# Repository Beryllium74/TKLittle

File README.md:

# TKLittle
My first custom keyboard layout, fully designed and created by me just as a fun learning experience.

The name TKLittle comes from the layout, inspiered by my 2 favorite layouts: Tkl and 40%(with a little opional HHKB-like bottom row thrown into in).

The pcb is made in Kicad 6 using Klepcbgen by Jeroen Bouwens as a starting point, but with a pro micro insted of an integrated chip.

The case is a top mounted stacked acrylic case made with the help of http://builder.swillkb.com/

Bottom layer, will be 3mm think in clear acrylic to show the bottom silkscreen of the pcb

Middle layer, 5mm thick frosted acrylic, with cutout wide enough to fit the pro micro so its closer to the edge so that it can use different cables easily

Plate, 3mm thick frosted acrylic, with 7u spacebar cutuouts and opion for non-HHKB layout

Top plate,5mm thick frosted acrylic with HHKB blockers.

The case should be mounted with 6 M2x18 bolts with nuts at the end, and for feen im gonna put some silicon feet instead of acyllic.

As i've said this is just a fun project, but i would like to learn from is it so i would if anyone with a bit more experience could give me some feedback on it before i spend the money to turn it into a reality
I have experience hand wiring multiple boards and ive made my own 3d printed cases before, so i kinda know what im doing, but its my first time working with Kicad so this is what im most worried about.

(obligatory language disclamer: english is not my first language so sorry if there are any spelling or grammar mistakes(but i do accept critisims as i need to get better)

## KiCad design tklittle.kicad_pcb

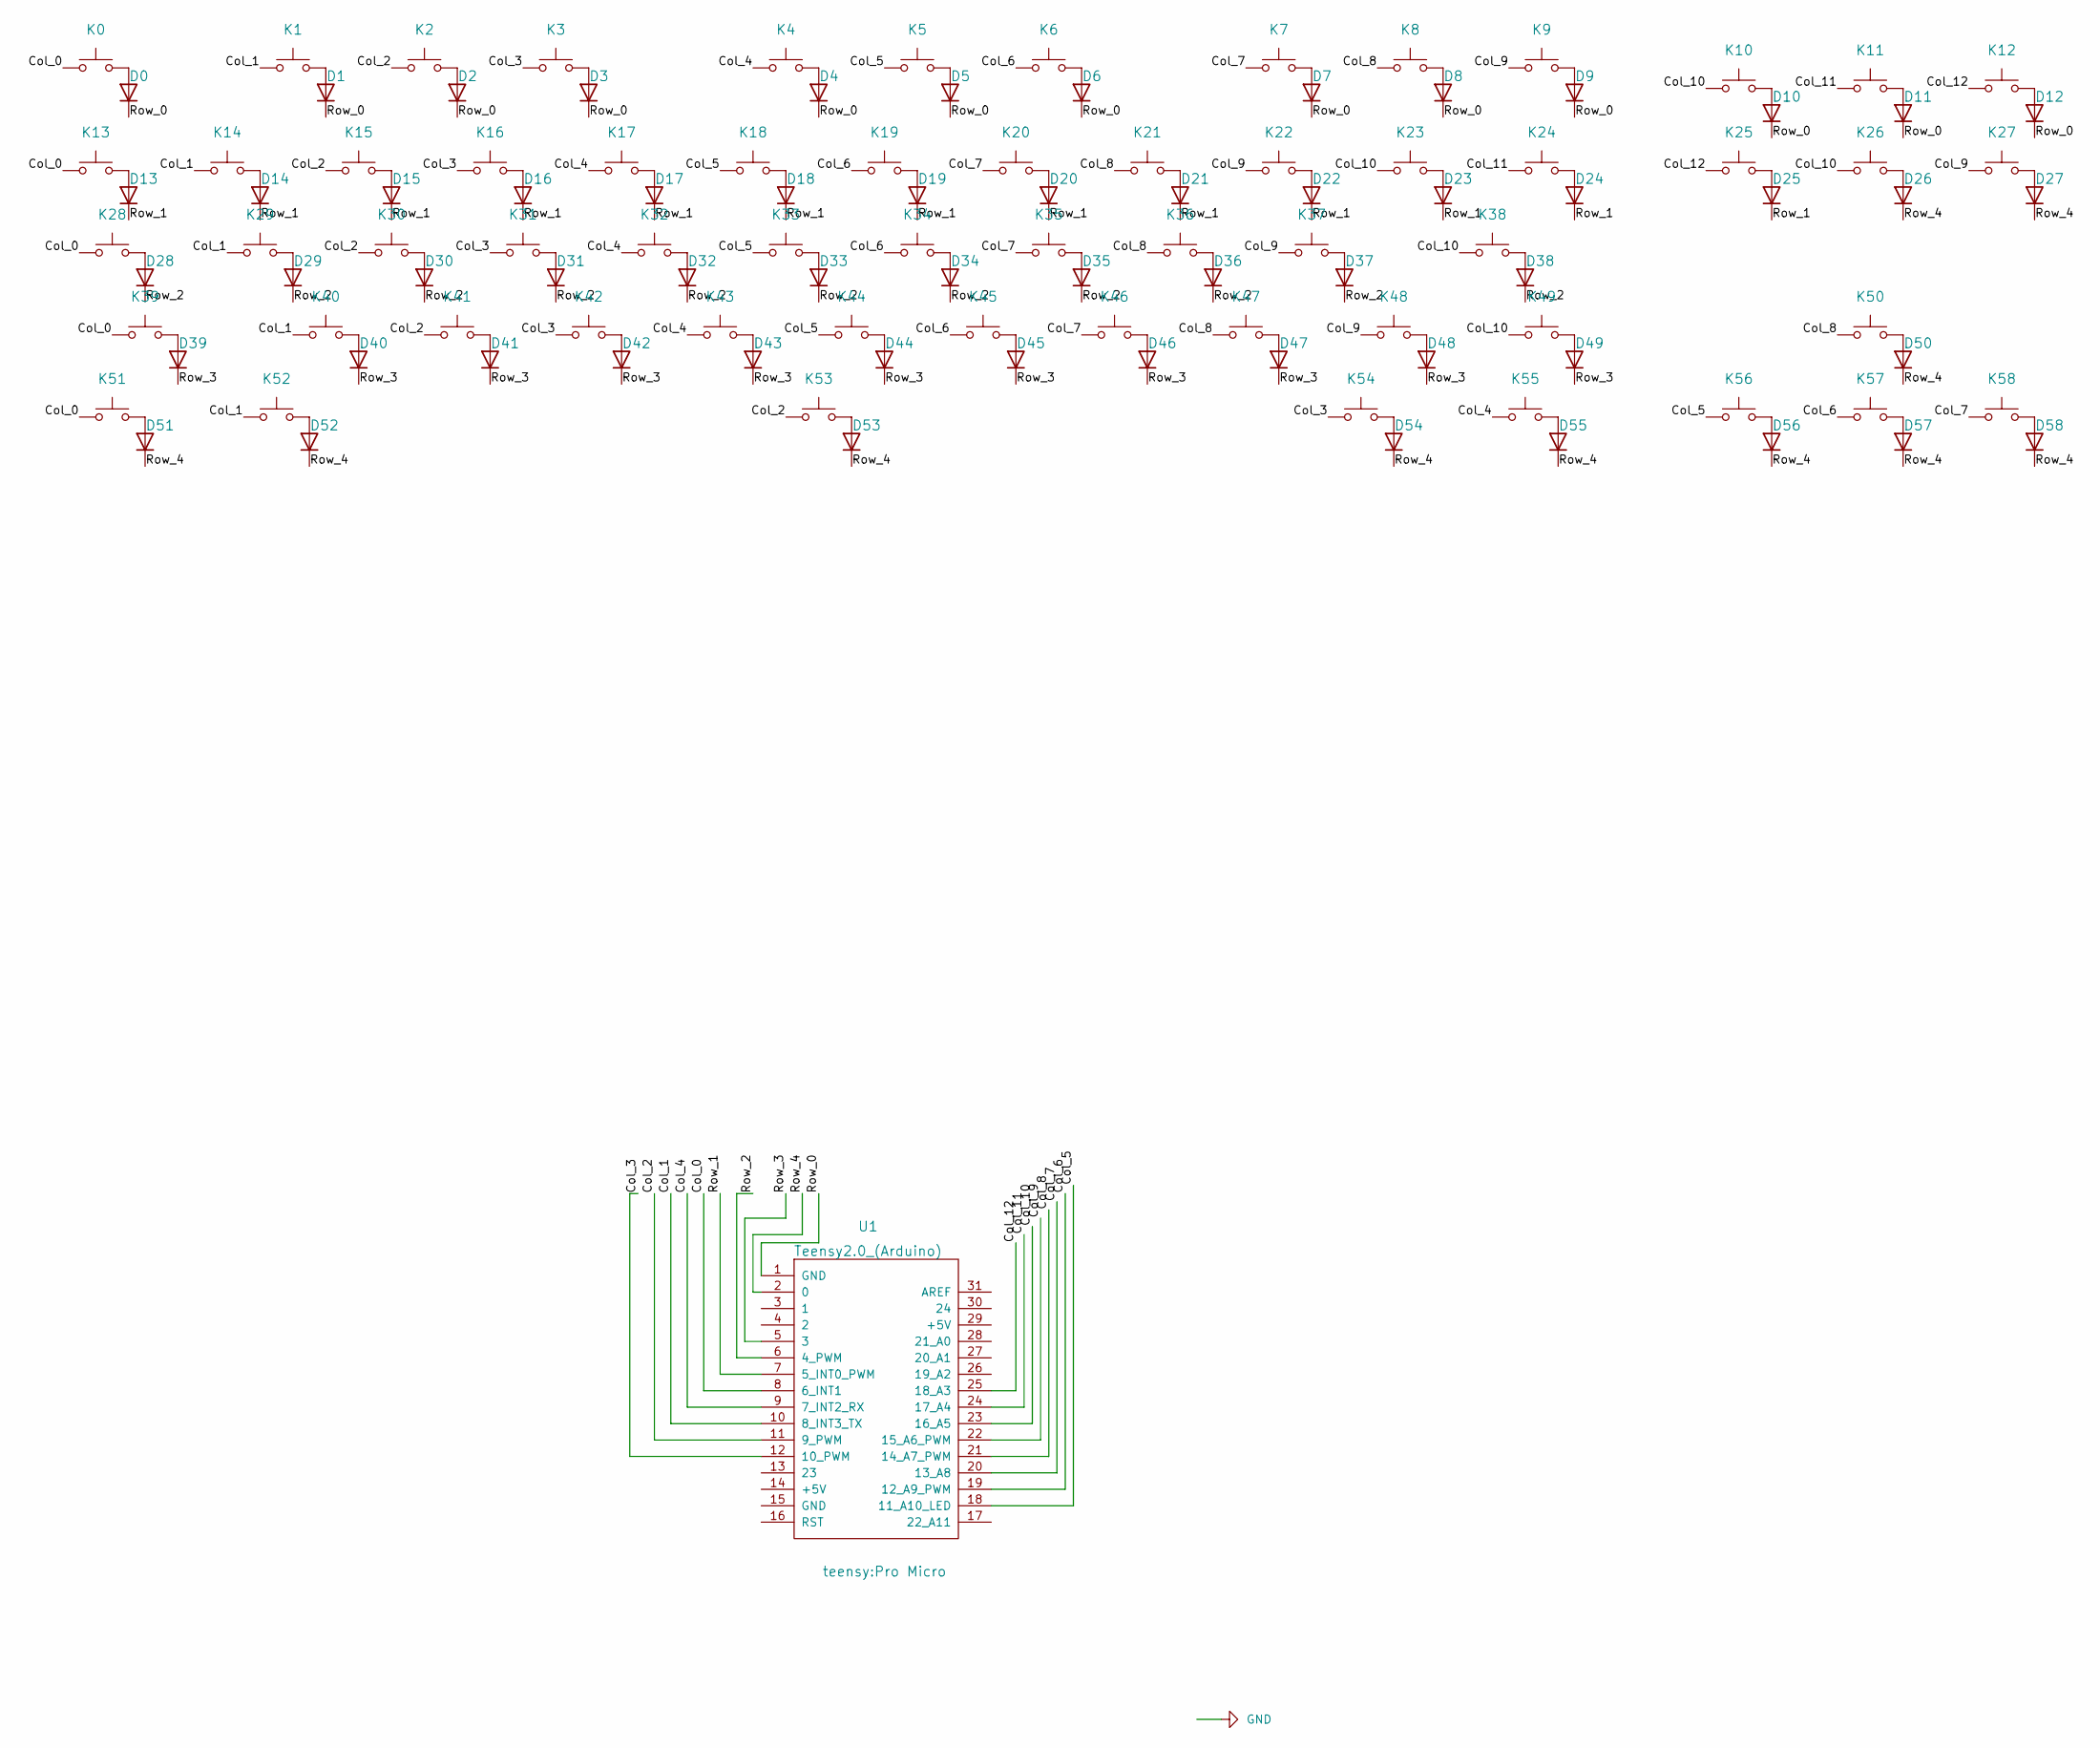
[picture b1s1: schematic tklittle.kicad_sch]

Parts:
D0, D1, D2, D3, D4, D5, D6, D7, D8, D9, D10, D11, D12, D13, D14, D15, D16, D17, D18, D19, D20, D21, D22, D23, D24, D25, D26, D27, D28, D29, D30, D31, D32, D33, D34, D35, D36, D37, D38, D39, D40, D41, D42, D43, D44, D45, D46, D47, D48, D49, D50, D51, D52, D53, D54, D55, D56, D57, D58: D; D_0805_2012Metric_Pad1.15x1.40mm_HandSolder
K0: 1; SW_Cherry_MX_1.00u_PCB
K1: 2; SW_Cherry_MX_1.00u_PCB
K2: 3; SW_Cherry_MX_1.00u_PCB
K3: 4; SW_Cherry_MX_1.00u_PCB
K4: 5; SW_Cherry_MX_1.00u_PCB
K5: 6; SW_Cherry_MX_1.00u_PCB
K6: 7; SW_Cherry_MX_1.00u_PCB
K7: 8; SW_Cherry_MX_1.00u_PCB
K8: 9; SW_Cherry_MX_1.00u_PCB
K9: 0; SW_Cherry_MX_1.00u_PCB
K10: insert; SW_Cherry_MX_1.00u_PCB
K11: Home; SW_Cherry_MX_1.00u_PCB
K12: Pgup; SW_Cherry_MX_1.00u_PCB
K13: Esc; SW_Cherry_MX_1.00u_PCB
K14: Q; SW_Cherry_MX_1.00u_PCB
K15: W; SW_Cherry_MX_1.00u_PCB
K16: E; SW_Cherry_MX_1.00u_PCB
K17: R; SW_Cherry_MX_1.00u_PCB
K18: T; SW_Cherry_MX_1.00u_PCB
K19: Y; SW_Cherry_MX_1.00u_PCB
K20: U; SW_Cherry_MX_1.00u_PCB
K21: I; SW_Cherry_MX_1.00u_PCB
K22: O; SW_Cherry_MX_1.00u_PCB
K23: P; SW_Cherry_MX_1.00u_PCB
K24: Back<br>Space; SW_Cherry_MX_1.00u_PCB
K25: Delete; SW_Cherry_MX_1.00u_PCB
K26: Emd; SW_Cherry_MX_1.00u_PCB
K27: PgDn; SW_Cherry_MX_1.00u_PCB
K28: Tab; SW_Cherry_MX_1.25u_PCB
K29: A; SW_Cherry_MX_1.00u_PCB
K30: S; SW_Cherry_MX_1.00u_PCB
K31: D; SW_Cherry_MX_1.00u_PCB
K32: F; SW_Cherry_MX_1.00u_PCB
K33: G; SW_Cherry_MX_1.00u_PCB
K34: H; SW_Cherry_MX_1.00u_PCB
K35: J; SW_Cherry_MX_1.00u_PCB
K36: K; SW_Cherry_MX_1.00u_PCB
K37: L; SW_Cherry_MX_1.00u_PCB
K38: Enter; SW_Cherry_MX_1.75u_PCB
K39: Shift; SW_Cherry_MX_1.75u_PCB
K40: Z; SW_Cherry_MX_1.00u_PCB
K41: X; SW_Cherry_MX_1.00u_PCB
K42: C; SW_Cherry_MX_1.00u_PCB
K43: V; SW_Cherry_MX_1.00u_PCB
K44: B; SW_Cherry_MX_1.00u_PCB
K45: N; SW_Cherry_MX_1.00u_PCB
K46: M; SW_Cherry_MX_1.00u_PCB
K47: <,.; SW_Cherry_MX_1.00u_PCB
K48: Shift; SW_Cherry_MX_1.25u_PCB
K49: Fn; SW_Cherry_MX_1.00u_PCB
K50: up; SW_Cherry_MX_1.00u_PCB
K51, K55: Super; SW_Cherry_MX_1.25u_PCB
K52, K54: Meta; SW_Cherry_MX_1.25u_PCB
K53: Blank; SW_Cherry_MX_6.25u_PCB
K56: left; SW_Cherry_MX_1.00u_PCB
K57: down; SW_Cherry_MX_1.00u_PCB
K58: right; SW_Cherry_MX_1.00u_PCB
U1: Teensy2.0_(Arduino); Pro Micro

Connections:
/Col_0: K0.1, K13.1, K28.1, K39.1, K51.1, U1.8 (6_INT1)
/Col_1: K1.1, K14.1, K29.1, K40.1, K52.1, U1.10 (8_INT3_TX)
/Col_2: K2.1, K15.1, K30.1, K41.1, K53.1, U1.11 (9_PWM)
/Col_3: K3.1, K16.1, K31.1, K42.1, K54.1, U1.12 (10_PWM)
/Col_4: K4.1, K17.1, K32.1, K43.1, K55.1, U1.9 (7_INT2_RX)
/Col_5: K5.1, K18.1, K33.1, K44.1, K56.1, U1.18 (11_A10_LED)
/Col_6: K6.1, K19.1, K34.1, K45.1, K57.1, U1.19 (12_A9_PWM)
/Col_7: K7.1, K20.1, K35.1, K46.1, K58.1, U1.20 (13_A8)
/Col_8: K8.1, K21.1, K36.1, K47.1, K50.1, U1.21 (14_A7_PWM)
/Col_9: K9.1, K22.1, K27.1, K37.1, K48.1, U1.22 (15_A6_PWM)
/Col_10: K10.1, K23.1, K26.1, K38.1, K49.1, U1.23 (16_A5)
/Col_11: K11.1, K24.1, U1.24 (17_A4)
/Col_12: K12.1, K25.1, U1.25 (18_A3)
/Row_0: D0.1 (K), D1.1 (K), D2.1 (K), D3.1 (K), D4.1 (K), D5.1 (K), D6.1 (K), D7.1 (K), D8.1 (K), D9.1 (K), D10.1 (K), D11.1 (K), D12.1 (K), U1.1 (GND)
/Row_1: D13.1 (K), D14.1 (K), D15.1 (K), D16.1 (K), D17.1 (K), D18.1 (K), D19.1 (K), D20.1 (K), D21.1 (K), D22.1 (K), D23.1 (K), D24.1 (K), D25.1 (K), U1.7 (5_INT0_PWM)
/Row_2: D28.1 (K), D29.1 (K), D30.1 (K), D31.1 (K), D32.1 (K), D33.1 (K), D34.1 (K), D35.1 (K), D36.1 (K), D37.1 (K), D38.1 (K), U1.6 (4_PWM)
/Row_3: D39.1 (K), D40.1 (K), D41.1 (K), D42.1 (K), D43.1 (K), D44.1 (K), D45.1 (K), D46.1 (K), D47.1 (K), D48.1 (K), D49.1 (K), U1.5 (3)
/Row_4: D26.1 (K), D27.1 (K), D50.1 (K), D51.1 (K), D52.1 (K), D53.1 (K), D54.1 (K), D55.1 (K), D56.1 (K), D57.1 (K), D58.1 (K), U1.2 (0)
unnamed: D0.2 (A), K0.2
unnamed: D1.2 (A), K1.2
unnamed: D2.2 (A), K2.2
unnamed: D3.2 (A), K3.2
unnamed: D4.2 (A), K4.2
unnamed: D5.2 (A), K5.2
unnamed: D6.2 (A), K6.2
unnamed: D7.2 (A), K7.2
unnamed: D8.2 (A), K8.2
unnamed: D9.2 (A), K9.2
unnamed: D10.2 (A), K10.2
unnamed: D11.2 (A), K11.2
unnamed: D12.2 (A), K12.2
unnamed: D13.2 (A), K13.2
unnamed: D14.2 (A), K14.2
unnamed: D15.2 (A), K15.2
unnamed: D16.2 (A), K16.2
unnamed: D17.2 (A), K17.2
unnamed: D18.2 (A), K18.2
unnamed: D19.2 (A), K19.2
unnamed: D20.2 (A), K20.2
unnamed: D21.2 (A), K21.2
unnamed: D22.2 (A), K22.2
unnamed: D23.2 (A), K23.2
unnamed: D24.2 (A), K24.2
unnamed: D25.2 (A), K25.2
unnamed: D26.2 (A), K26.2
unnamed: D27.2 (A), K27.2
unnamed: D28.2 (A), K28.2
unnamed: D29.2 (A), K29.2
unnamed: D30.2 (A), K30.2
unnamed: D31.2 (A), K31.2
unnamed: D32.2 (A), K32.2
unnamed: D33.2 (A), K33.2
unnamed: D34.2 (A), K34.2
unnamed: D35.2 (A), K35.2
unnamed: D36.2 (A), K36.2
unnamed: D37.2 (A), K37.2
unnamed: D38.2 (A), K38.2
unnamed: D39.2 (A), K39.2
unnamed: D40.2 (A), K40.2
unnamed: D41.2 (A), K41.2
unnamed: D42.2 (A), K42.2
unnamed: D43.2 (A), K43.2
unnamed: D44.2 (A), K44.2
unnamed: D45.2 (A), K45.2
unnamed: D46.2 (A), K46.2
unnamed: D47.2 (A), K47.2
unnamed: D48.2 (A), K48.2
unnamed: D49.2 (A), K49.2
unnamed: D50.2 (A), K50.2
unnamed: D51.2 (A), K51.2
unnamed: D52.2 (A), K52.2
unnamed: D53.2 (A), K53.2
unnamed: D54.2 (A), K54.2
unnamed: D55.2 (A), K55.2
unnamed: D56.2 (A), K56.2
unnamed: D57.2 (A), K57.2
unnamed: D58.2 (A), K58.2

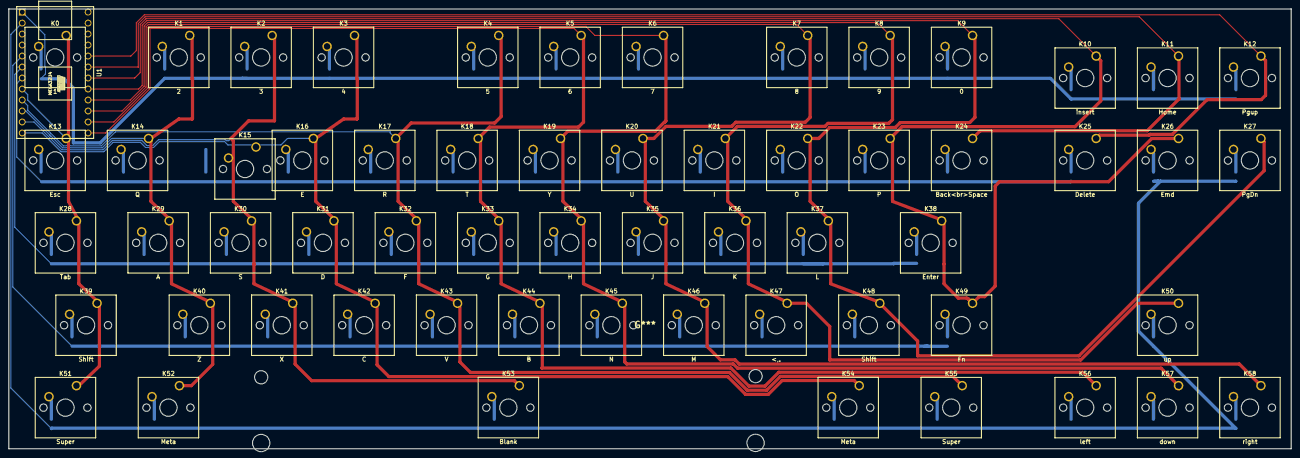
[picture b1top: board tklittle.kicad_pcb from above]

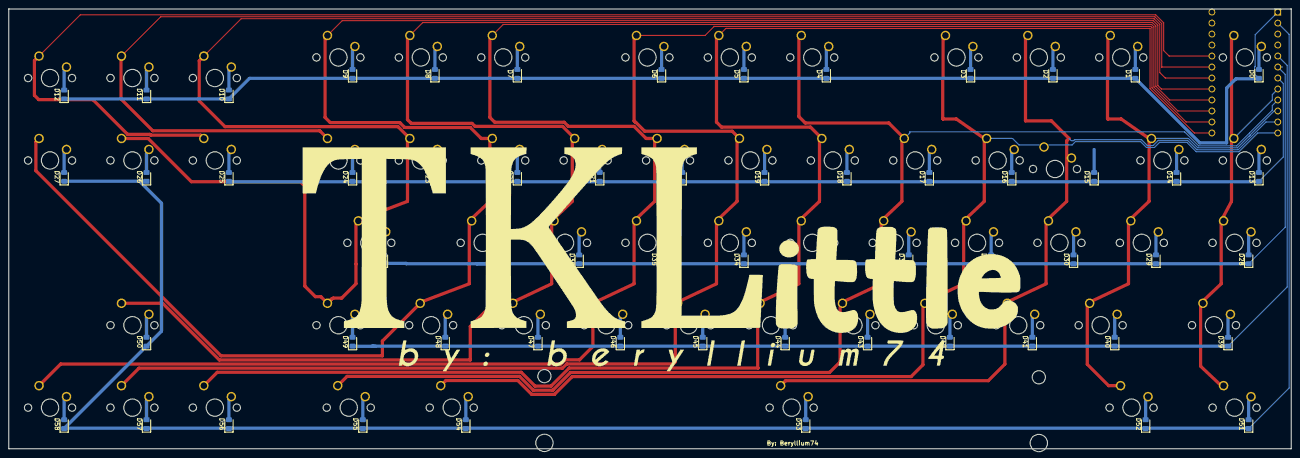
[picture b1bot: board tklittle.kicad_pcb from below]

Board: 2 copper layers, 296.5 x 101.7 mm, 119 parts (59 on the bottom side), 77 nets.
